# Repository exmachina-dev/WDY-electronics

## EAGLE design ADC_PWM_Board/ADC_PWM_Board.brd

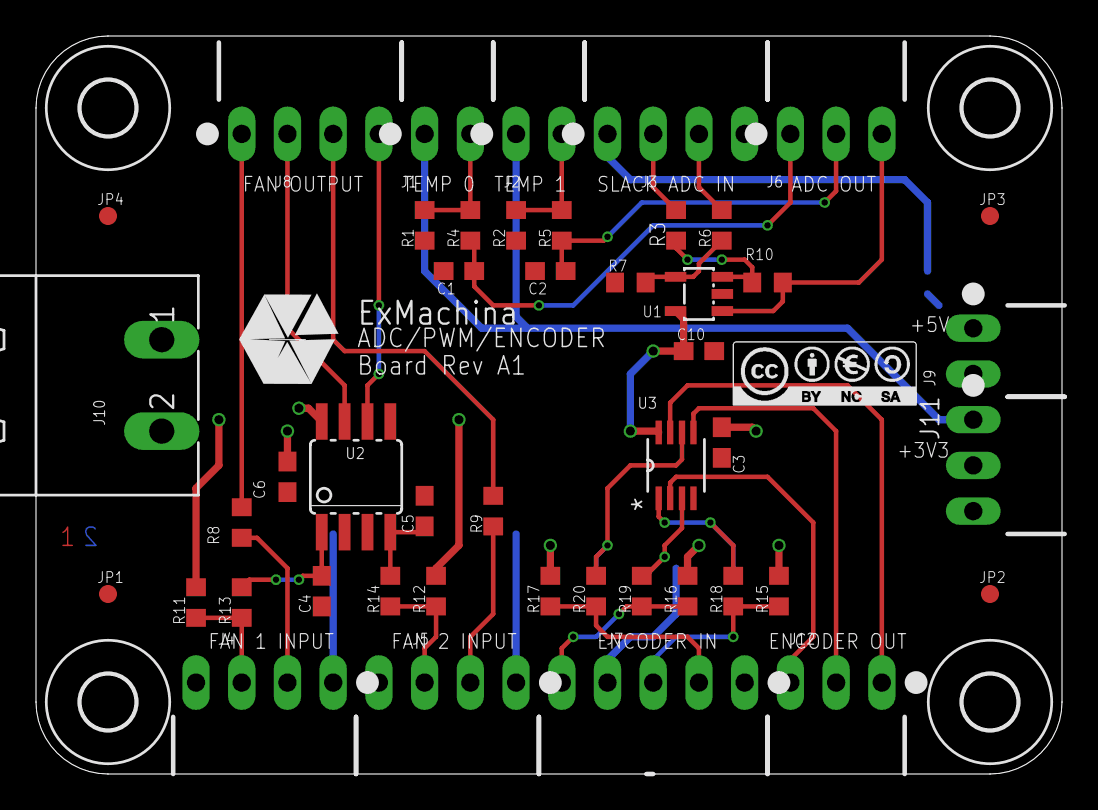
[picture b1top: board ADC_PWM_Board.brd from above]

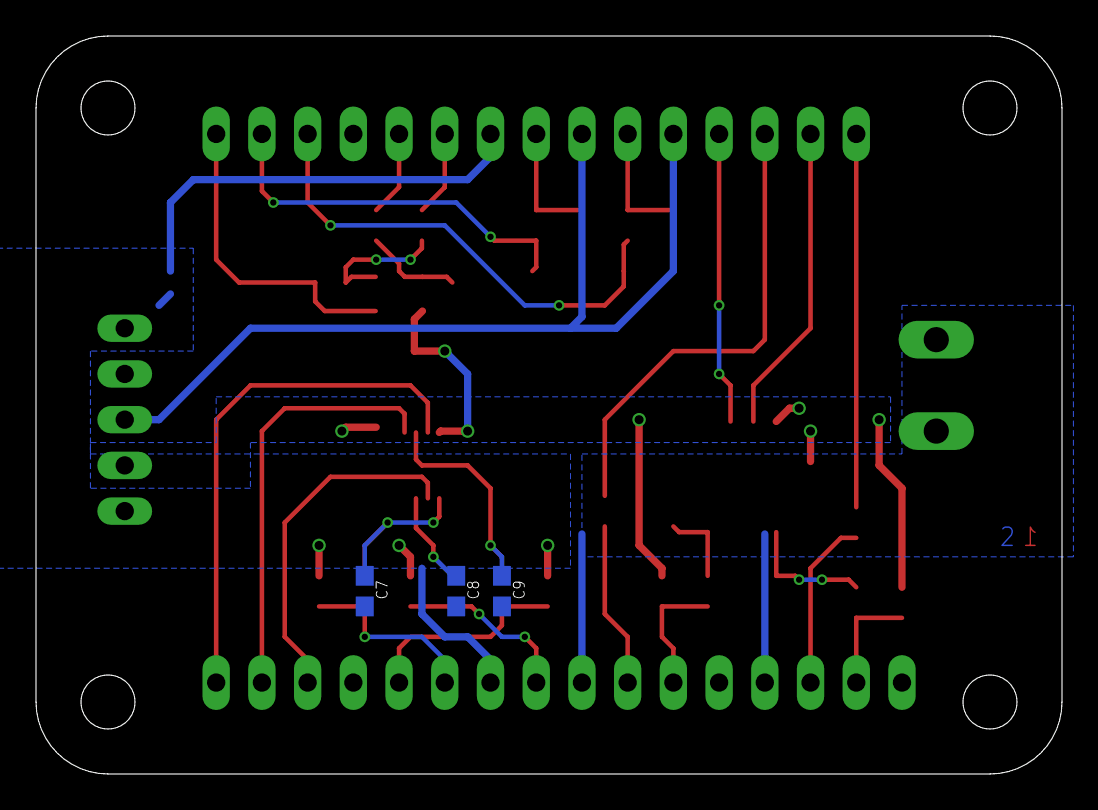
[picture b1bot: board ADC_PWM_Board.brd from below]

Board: 2 copper layers, 57.0 x 41.0 mm, 55 parts (3 on the bottom side), 33 nets.

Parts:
C1, C2, C3, C4, C5, C6, C7, C8, C9, C10: 0.1uF; C0603
CC1: CC-BY-NC-SA
H1, H2, H3, H4: MOUNT-HOLE3.0; 3,0
J1, J2, J9: 22-05-7028-02; 7395-02
J3, J4, J5, J8: 22-05-7048-04; 7395-04
J6, J11, J12: 22-05-7038-03; 7395-03
J7: 22-05-7058-05; 7395-05
J10: MSTBA2
JP1, JP2, JP3, JP4: FIDUCIAL1X2; FIDUCIAL-1X2
R1, R2: 10K; R0603
R3, R6: 1K8; R0603
R4, R5, R8, R9, R11, R12: 1K; R0603
R7, R10: 1K2; R0603
R13, R14, R18, R19, R20: 100; R0603
R15, R16, R17: 2K7; R0603
T1: EXMACHINA-LOGO-NAME; EXM-LOGO-BASELINE
U1: TLV313; SOT23-DBV
U2: HCPL0631; SOIC08
U3: SN74LVC3G17DCTR; SOP65P400X130-8N

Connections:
+3V3: C3.1, C6.1, C10.1, J11.2, R11.2, R12.2, U1.5, U2.8, U3.8
+5V: J3.1, J7.4, J9.1, R15.1, R16.1, R17.1
+24V: J4.1, J5.1, J10.1
ADC_SLACK_DETECTION: J6.3, R10.1, U1.1
ADC_TEMP_0: C1.1, J6.1, R4.1
ADC_TEMP_1: C2.1, J6.2, R5.2
AVDD: J1.1, J2.1, J11.1
ENCODER_A: J12.1, U3.7
ENCODER_B: J12.2, U3.5
ENCODER_Z: J12.3, U3.2
FAN_1_PWM: J8.1, R8.2
FAN_1_SENSOR: J8.2, U2.7
FAN_2_PWM: J8.3, R9.2
FAN_2_SENSOR: J8.4, U2.6
GND: C1.2, C2.2, C3.2, C4.2, C5.2, C6.2, C7.2, C8.2, C9.2, C10.2, J3.4, J4.4, J5.4, J7.1, J9.2, J10.2, J11.3, R1.1, R2.2, R7.1, U1.2, U2.2, U2.3, U2.5, U3.4
unnamed: J4.3, R11.1, R13.1
unnamed: J5.3, R12.1, R14.1
unnamed: C4.1, R13.2, U2.1
unnamed: C5.1, R14.2, U2.4
unnamed: J4.2, R8.1
unnamed: J5.2, R9.1
unnamed: J3.2, R3.1
unnamed: J7.3, R15.2, R18.1
unnamed: J7.5, R16.2, R19.1
unnamed: J7.2, R17.2, R20.1
unnamed: C9.1, R20.2, U3.6
unnamed: C8.1, R19.2, U3.3
unnamed: C7.1, R18.2, U3.1
unnamed: R3.2, R10.2, U1.3
unnamed: J1.2, R1.2, R4.2
unnamed: J2.2, R2.1, R5.1
unnamed: R6.2, R7.2, U1.4
unnamed: J3.3, R6.1

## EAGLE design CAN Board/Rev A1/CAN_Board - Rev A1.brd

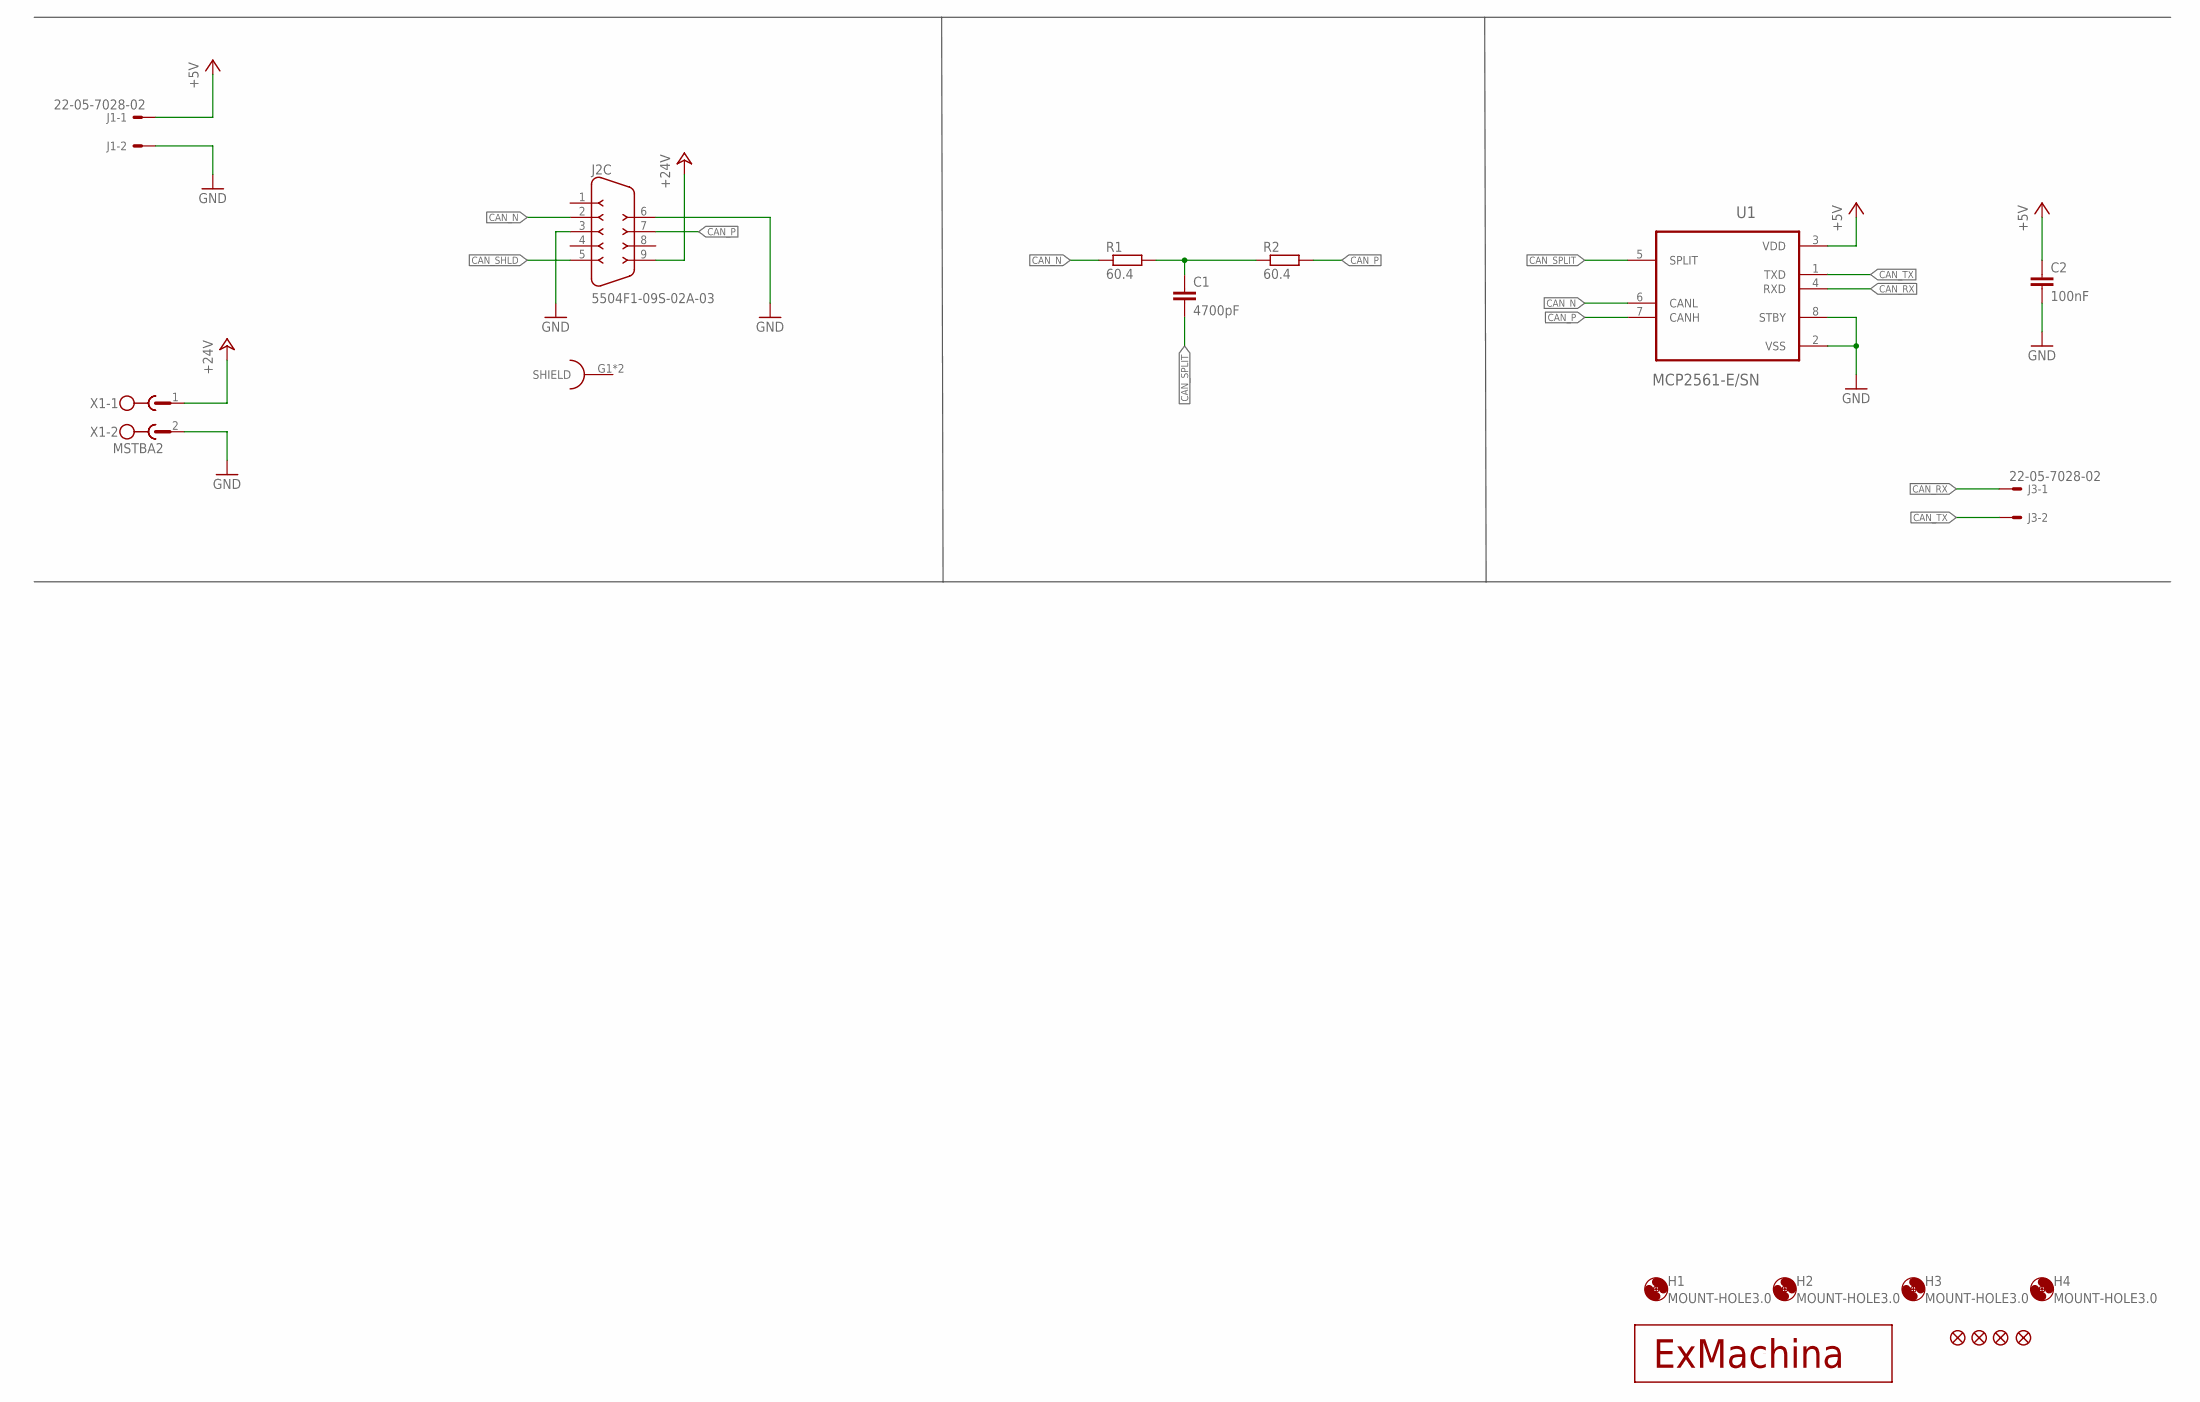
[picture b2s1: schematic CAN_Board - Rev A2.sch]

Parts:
C1: 4700pF; C0603; MPN MC0603B472K500CT
C2: 100nF; C0603; MPN MC0603B104K250CT
H1, H2, H3, H4: MOUNT-HOLE3.0; 3,0
J1, J3: 22-05-7028-02; 7395-02; MPN 22-05-7028
J2: 5504F1-09S-02A-03; 5504F1-09S-02A; MPN 5504F1-09S-02A-03
JP1, JP2, JP3, JP4: FIDUCIAL1X2; FIDUCIAL-1X2
R1, R2: 60.4; R0603; MPN MCMR06X60R4FTL
T1: EXMACHINA-LOGO-NAME; EXM-LOGO-BASELINE
U1: MCP2561-E/SN; SOIC127P600X175-8N; MPN MCP2561-E/SN
X1: MSTBA2

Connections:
+3V3: C2.1, J1.1, U1.3 (VDD)
+24V: J2.9, X1.1
CAN_N: J2.2, R1.1, U1.6 (CANL)
CAN_P: J2.7, R2.2, U1.7 (CANH)
CAN_RX: J3.1, U1.4 (RXD)
CAN_SHLD: J2.5
CAN_SPLIT: C1.2, U1.5 (SPLIT)
CAN_TX: J3.2, U1.1 (TXD)
GND: C2.2, J1.2, J2.3, J2.6, U1.2 (VSS), U1.8 (STBY), X1.2
unnamed: C1.1, R1.2, R2.1

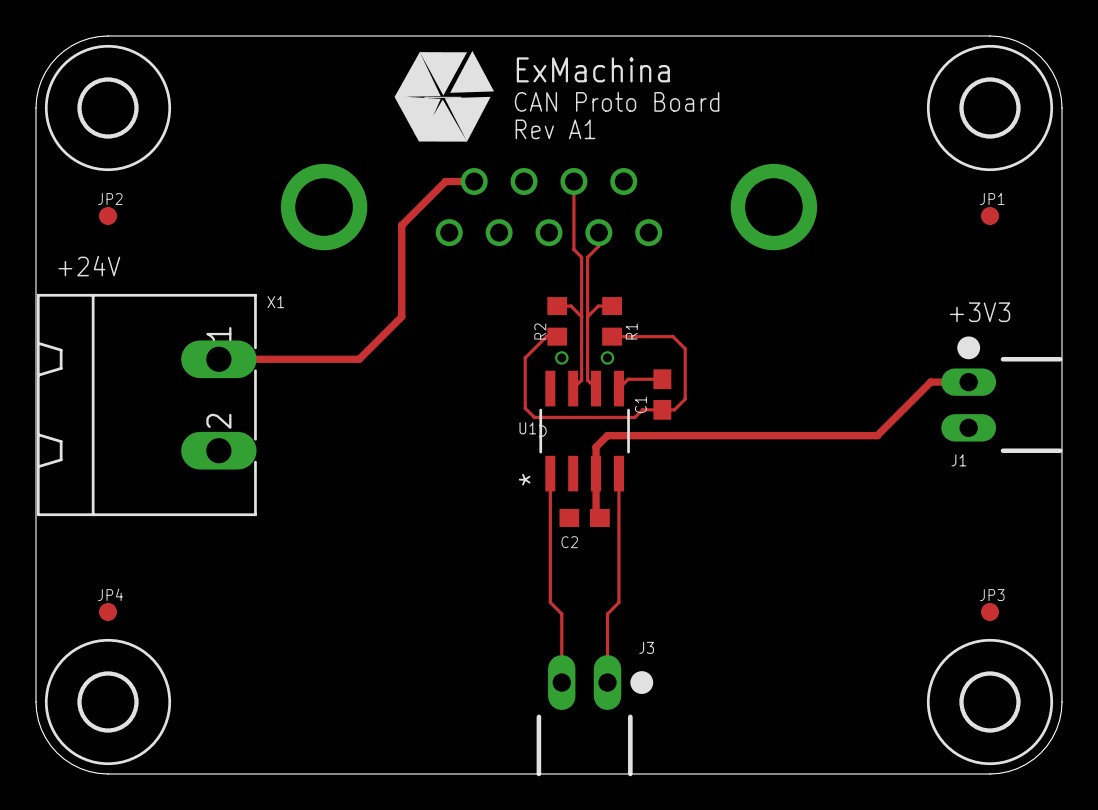
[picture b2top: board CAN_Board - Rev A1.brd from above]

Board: 2 copper layers, 57.0 x 41.0 mm, 18 parts (1 on the bottom side), 9 nets.

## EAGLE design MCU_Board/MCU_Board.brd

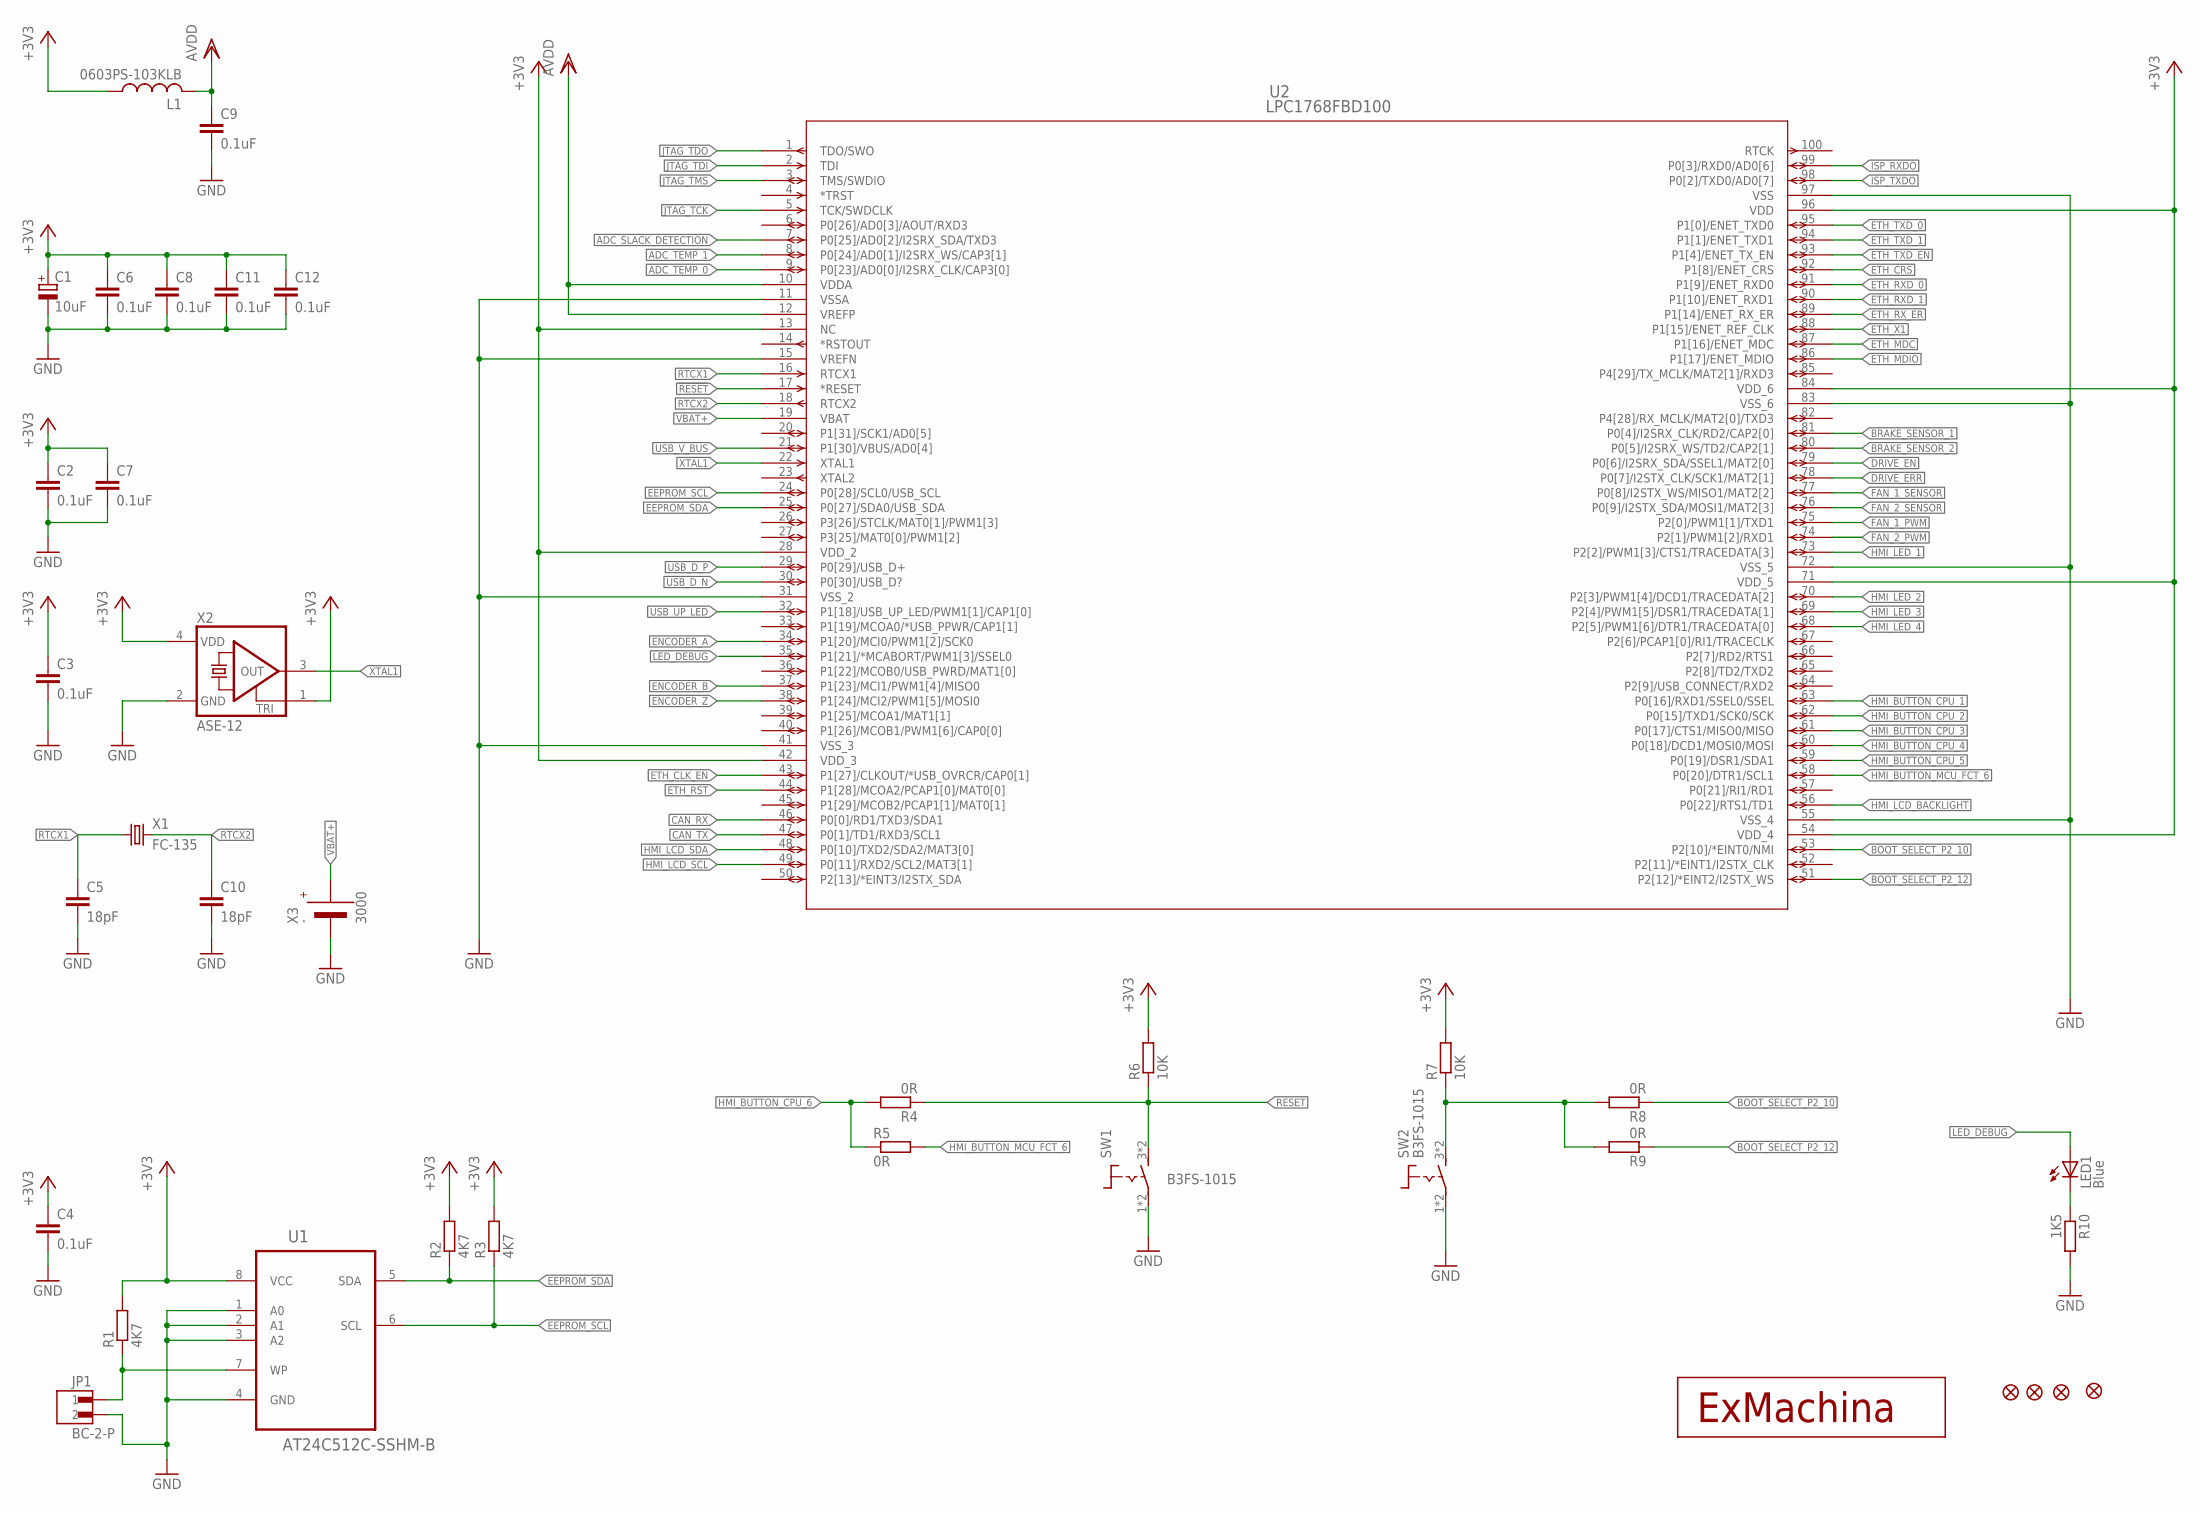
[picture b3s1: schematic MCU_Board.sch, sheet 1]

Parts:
C1: 10uF; CT3216
C2, C3, C4, C6, C7, C8, C9, C11, C12: 0.1uF; C0603
C5, C10: 18pF; C0603
JP1: BC-2-P
JP2, JP3, JP4, JP5: FIDUCIAL1X2; FIDUCIAL-1X2
L1: 0603PS-103KLB; 0603
LED1: Blue; CHIPLED_0603
R1, R2, R3: 4K7; R0603
R4, R5, R8, R9: 0R; R0603
R6, R7: 10K; R0603
R10: 1K5; R0603
SW1, SW2: B3FS-1015; B3FS
T2: EXMACHINA-LOGO-NAME; EXM-LOGO-BASELINE
U1: AT24C512C-SSHM-B; SOIC127P600X175-8N
U2: LPC1768FBD100; SOT407-1
X1: FC-135
X2: ASE-12; ASE
X3: 3000

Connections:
!RESET: U2.17 (*RESET)
ADC_SLACK_DETECTION: U2.7 (P0[25]/AD0[2]/I2SRX_SDA/TXD3); also elsewhere on the board
ADC_TEMP_0: U2.9 (P0[23]/AD0[0]/I2SRX_CLK/CAP3[0]); also elsewhere on the board
ADC_TEMP_1: U2.8 (P0[24]/AD0[1]/I2SRX_WS/CAP3[1]); also elsewhere on the board
BOOT_SELECT_P2_10: R8.1, U2.53 (P2[10]/*EINT0/NMI)
BOOT_SELECT_P2_12: R9.1, U2.51 (P2[12]/*EINT2/I2STX_WS)
BRAKE_SENSOR_1: U2.81 (P0[4]/I2SRX_CLK/RD2/CAP2[0]); also elsewhere on the board
BRAKE_SENSOR_2: U2.80 (P0[5]/I2SRX_WS/TD2/CAP2[1]); also elsewhere on the board
CAN_RX: U2.46 (P0[0]/RD1/TXD3/SDA1); also elsewhere on the board
CAN_TX: U2.47 (P0[1]/TD1/RXD3/SCL1); also elsewhere on the board
DRIVE_EN: U2.79 (P0[6]/I2SRX_SDA/SSEL1/MAT2[0]); also elsewhere on the board
DRIVE_ERR: U2.78 (P0[7]/I2STX_CLK/SCK1/MAT2[1]); also elsewhere on the board
EEPROM_SCL: R3.1, U1.6 (SCL), U2.24 (P0[28]/SCL0/USB_SCL)
EEPROM_SDA: R2.1, U1.5 (SDA), U2.25 (P0[27]/SDA0/USB_SDA)
ENCODER_A: U2.34 (P1[20]/MCI0/PWM1[2]/SCK0); also elsewhere on the board
ENCODER_B: U2.37 (P1[23]/MCI1/PWM1[4]/MISO0); also elsewhere on the board
ENCODER_Z: U2.38 (P1[24]/MCI2/PWM1[5]/MOSI0); also elsewhere on the board
ETH_CLK_EN: U2.43 (P1[27]/CLKOUT/*USB_OVRCR/CAP0[1])
ETH_CRS: U2.92 (P1[8]/ENET_CRS); also elsewhere on the board
ETH_MDC: U2.87 (P1[16]/ENET_MDC); also elsewhere on the board
ETH_MDIO: U2.86 (P1[17]/ENET_MDIO); also elsewhere on the board
ETH_RST: U2.44 (P1[28]/MCOA2/PCAP1[0]/MAT0[0]); also elsewhere on the board
ETH_RXD_0: U2.91 (P1[9]/ENET_RXD0); also elsewhere on the board
ETH_RXD_1: U2.90 (P1[10]/ENET_RXD1); also elsewhere on the board
ETH_RX_ER: U2.89 (P1[14]/ENET_RX_ER); also elsewhere on the board
ETH_TXD_0: U2.95 (P1[0]/ENET_TXD0); also elsewhere on the board
ETH_TXD_1: U2.94 (P1[1]/ENET_TXD1); also elsewhere on the board
ETH_TXD_EN: U2.93 (P1[4]/ENET_TX_EN); also elsewhere on the board
ETH_X1: U2.88 (P1[15]/ENET_REF_CLK); also elsewhere on the board
FAN_1_PWM: U2.75 (P2[0]/PWM1[1]/TXD1); also elsewhere on the board
FAN_1_SENSOR: U2.77 (P0[8]/I2STX_WS/MISO1/MAT2[2]); also elsewhere on the board
FAN_2_PWM: U2.74 (P2[1]/PWM1[2]/RXD1); also elsewhere on the board
FAN_2_SENSOR: U2.76 (P0[9]/I2STX_SDA/MOSI1/MAT2[3]); also elsewhere on the board
HMI_BUTTON_CPU_1: U2.63 (P0[16]/RXD1/SSEL0/SSEL); also elsewhere on the board
HMI_BUTTON_CPU_2: U2.62 (P0[15]/TXD1/SCK0/SCK); also elsewhere on the board
HMI_BUTTON_CPU_3: U2.61 (P0[17]/CTS1/MISO0/MISO); also elsewhere on the board
HMI_BUTTON_CPU_4: U2.60 (P0[18]/DCD1/MOSI0/MOSI); also elsewhere on the board
HMI_BUTTON_CPU_5: U2.59 (P0[19]/DSR1/SDA1); also elsewhere on the board
HMI_BUTTON_CPU_6: R4.2, R5.1; also elsewhere on the board
HMI_BUTTON_MCU_FCT_6: R5.2, U2.58 (P0[20]/DTR1/SCL1)
HMI_LCD_BACKLIGHT: U2.56 (P0[22]/RTS1/TD1); also elsewhere on the board
HMI_LCD_SCL: U2.49 (P0[11]/RXD2/SCL2/MAT3[1]); also elsewhere on the board
HMI_LCD_SDA: U2.48 (P0[10]/TXD2/SDA2/MAT3[0]); also elsewhere on the board
HMI_LED_1: U2.73 (P2[2]/PWM1[3]/CTS1/TRACEDATA[3]); also elsewhere on the board
HMI_LED_2: U2.70 (P2[3]/PWM1[4]/DCD1/TRACEDATA[2]); also elsewhere on the board
HMI_LED_3: U2.69 (P2[4]/PWM1[5]/DSR1/TRACEDATA[1]); also elsewhere on the board
HMI_LED_4: U2.68 (P2[5]/PWM1[6]/DTR1/TRACEDATA[0]); also elsewhere on the board
ISP_RXDO: U2.99 (P0[3]/RXD0/AD0[6]); also elsewhere on the board
ISP_TXDO: U2.98 (P0[2]/TXD0/AD0[7]); also elsewhere on the board
JTAG_TCK: U2.5 (TCK/SWDCLK); also elsewhere on the board
JTAG_TDI: U2.2 (TDI); also elsewhere on the board
JTAG_TDO: U2.1 (TDO/SWO); also elsewhere on the board
JTAG_TMS: U2.3 (TMS/SWDIO); also elsewhere on the board
LED_DEBUG: LED1.A, U2.35 (P1[21]/*MCABORT/PWM1[3]/SSEL0)
unnamed: R7.1, R8.2, R9.2, SW2.3 (1), SW2.4 (1)
unnamed: JP1.1, R1.1, U1.7 (WP)
unnamed: LED1.C, R10.1
RESET: R4.1, R6.1, SW1.3 (1), SW1.4 (1); also elsewhere on the board
RTCX1: C5.1, U2.16 (RTCX1), X1.1
RTCX2: C10.1, U2.18 (RTCX2), X1.2
USB_D_N: U2.30 (P0[30]/USB_D?); also elsewhere on the board
USB_D_P: U2.29 (P0[29]/USB_D+); also elsewhere on the board
USB_UP_LED: U2.32 (P1[18]/USB_UP_LED/PWM1[1]/CAP1[0]); also elsewhere on the board
USB_V_BUS: U2.21 (P1[30]/VBUS/AD0[4]); also elsewhere on the board
VBAT+: U2.19 (VBAT), X3.+1 (VBAT+), X3.+2 (VBAT+)
XTAL1: U2.22 (XTAL1), X2.3 (OUT)

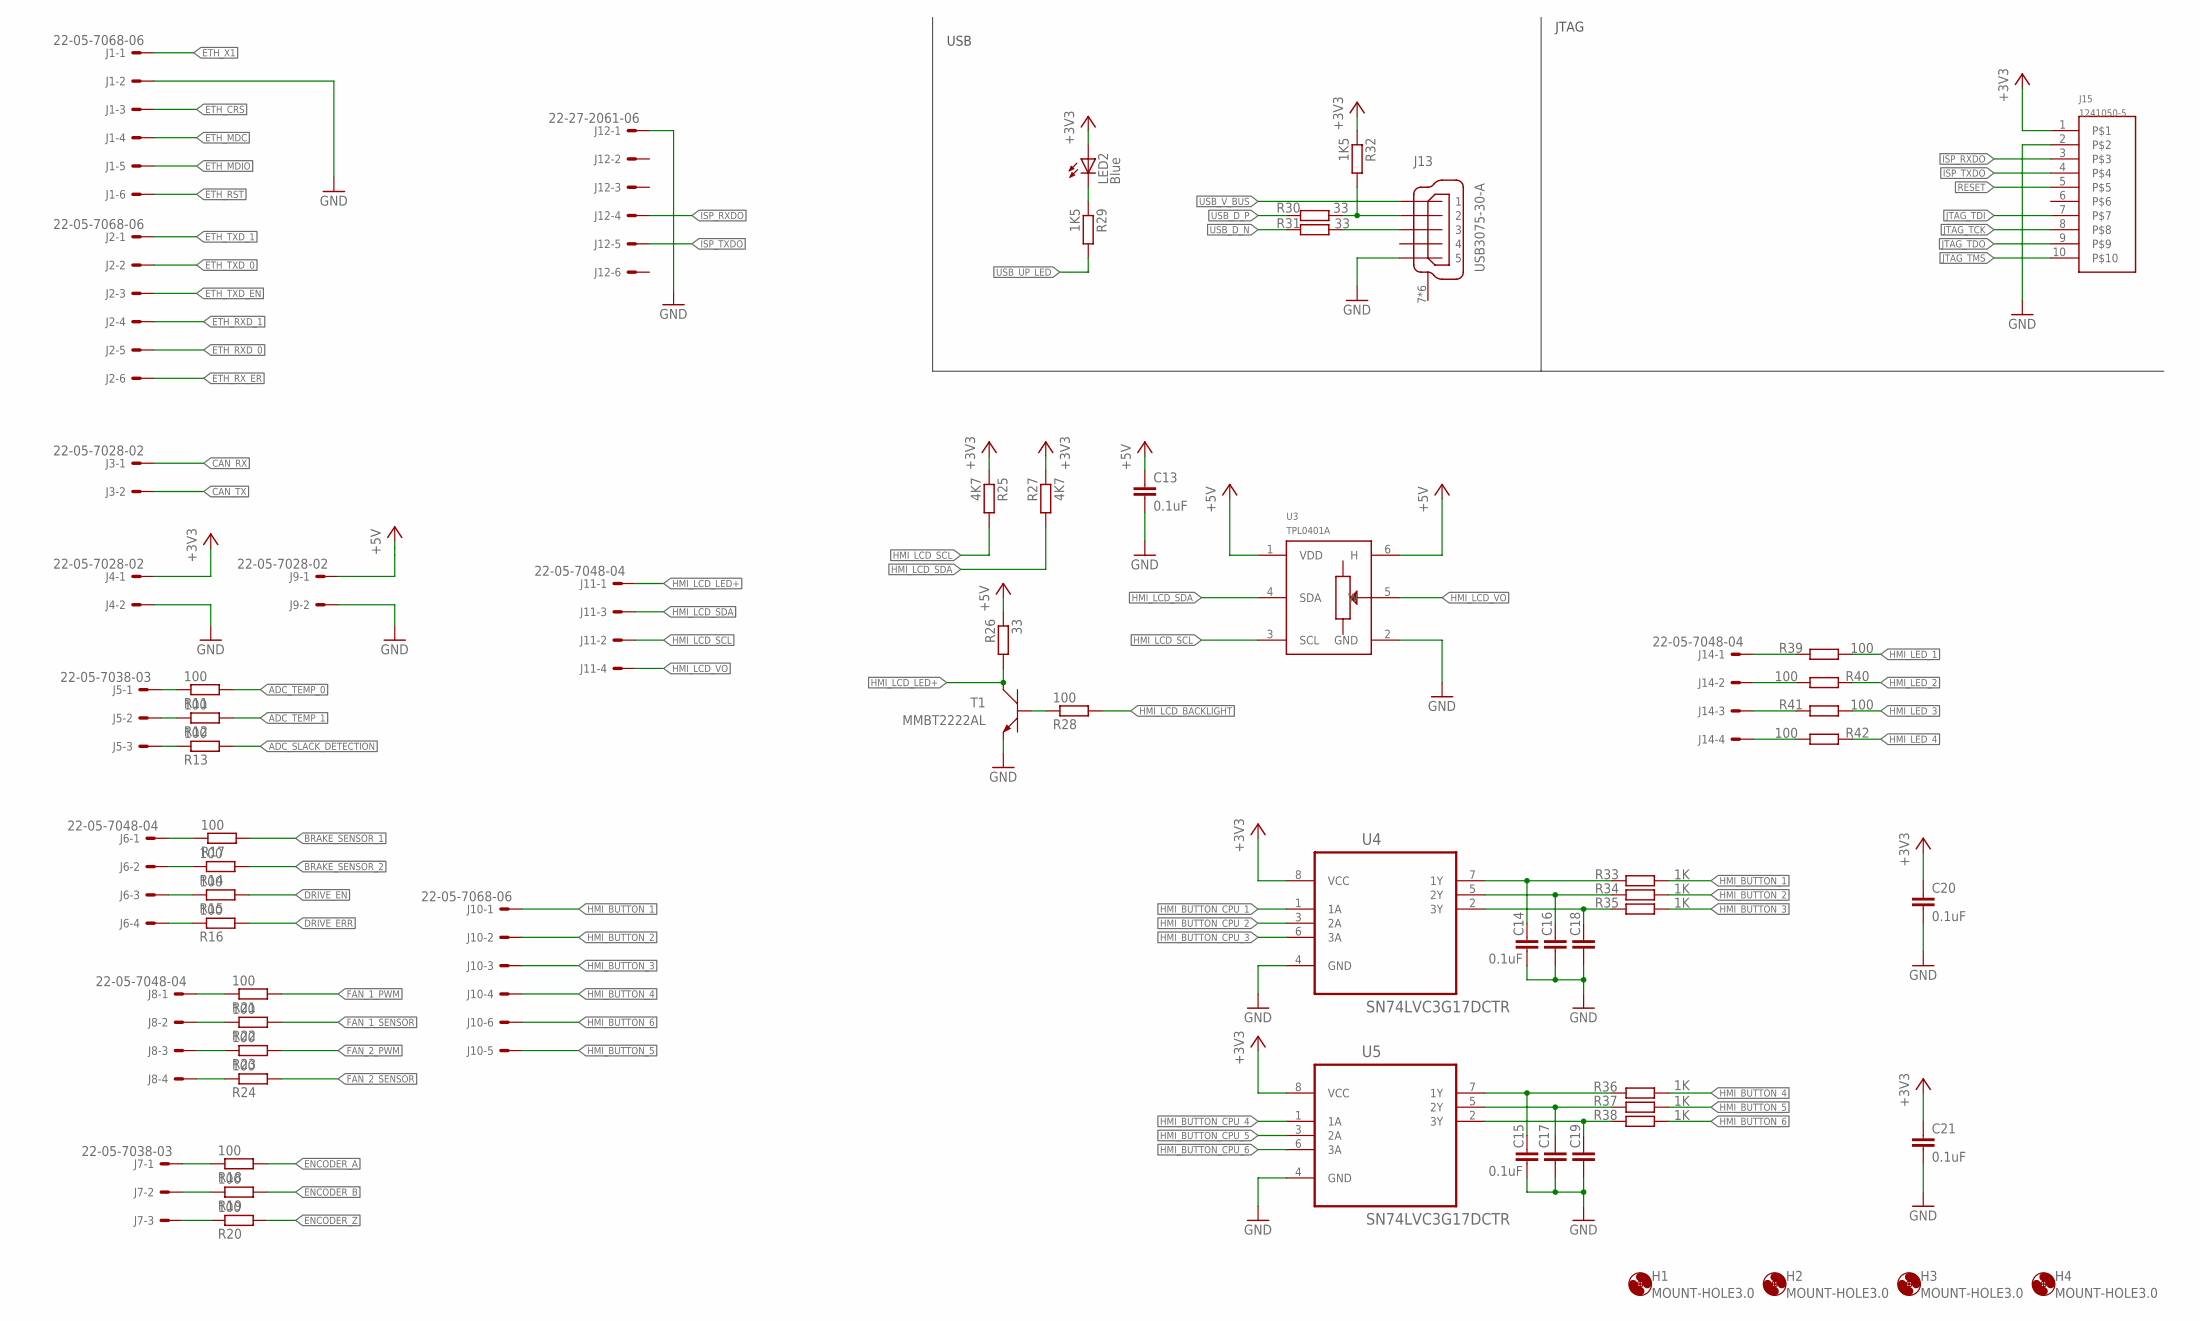
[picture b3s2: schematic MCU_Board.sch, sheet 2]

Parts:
C13, C14, C15, C16, C17, C18, C19, C20, C21: 0.1uF; C0603
H1, H2, H3, H4: MOUNT-HOLE3.0; 3,0
J1, J2, J10: 22-05-7068-06; 7395-06
J3, J4, J9: 22-05-7028-02; 7395-02
J5, J7: 22-05-7038-03; 7395-03
J6, J8, J11, J14: 22-05-7048-04; 7395-04
J12: 22-27-2061-06; 6410-06
J13: USB3075-30-A; USB_MICROB_SMT
J15: 1241050-5; 2.54/2X5
LED2: Blue; CHIPLED_0603
R11, R12, R13, R14, R15, R16, R17, R18, R19, R20, R21, R22, R23, R24, R28, R39, R40, R41, R42: 100; R0603
R25, R27: 4K7; R0603
R26, R30, R31: 33; R0603
R29, R32: 1K5; R0603
R33, R34, R35, R36, R37, R38: 1K; R0603
T1: MMBT2222AL; SOT−23
U3: TPL0401A; SC-70-DCK
U4, U5: SN74LVC3G17DCTR; SOP65P400X130-8N

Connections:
+5V: C13.1, J9.1, R26.1, U3.1 (VDD), U3.6 (H)
ADC_SLACK_DETECTION: R13.2; also elsewhere on the board
ADC_TEMP_0: R11.2; also elsewhere on the board
ADC_TEMP_1: R12.2; also elsewhere on the board
BRAKE_SENSOR_1: R17.2; also elsewhere on the board
BRAKE_SENSOR_2: R14.2; also elsewhere on the board
CAN_RX: J3.1; also elsewhere on the board
CAN_TX: J3.2; also elsewhere on the board
DRIVE_EN: R15.2; also elsewhere on the board
DRIVE_ERR: R16.2; also elsewhere on the board
ENCODER_A: R18.2; also elsewhere on the board
ENCODER_B: R19.2; also elsewhere on the board
ENCODER_Z: R20.2; also elsewhere on the board
ETH_CRS: J1.3; also elsewhere on the board
ETH_MDC: J1.4; also elsewhere on the board
ETH_MDIO: J1.5; also elsewhere on the board
ETH_RST: J1.6; also elsewhere on the board
ETH_RXD_0: J2.5; also elsewhere on the board
ETH_RXD_1: J2.4; also elsewhere on the board
ETH_RX_ER: J2.6; also elsewhere on the board
ETH_TXD_0: J2.2; also elsewhere on the board
ETH_TXD_1: J2.1; also elsewhere on the board
ETH_TXD_EN: J2.3; also elsewhere on the board
ETH_X1: J1.1; also elsewhere on the board
FAN_1_PWM: R21.2; also elsewhere on the board
FAN_1_SENSOR: R22.2; also elsewhere on the board
FAN_2_PWM: R23.2; also elsewhere on the board
FAN_2_SENSOR: R24.2; also elsewhere on the board
HMI_BUTTON_1: J10.1, R33.1
HMI_BUTTON_2: J10.2, R34.1
HMI_BUTTON_3: J10.3, R35.1
HMI_BUTTON_4: J10.4, R36.1
HMI_BUTTON_5: J10.5, R37.1
HMI_BUTTON_6: J10.6, R38.1
HMI_BUTTON_CPU_1: U4.1 (1A); also elsewhere on the board
HMI_BUTTON_CPU_2: U4.3 (2A); also elsewhere on the board
HMI_BUTTON_CPU_3: U4.6 (3A); also elsewhere on the board
HMI_BUTTON_CPU_4: U5.1 (1A); also elsewhere on the board
HMI_BUTTON_CPU_5: U5.3 (2A); also elsewhere on the board
HMI_BUTTON_CPU_6: U5.6 (3A); also elsewhere on the board
HMI_LCD_BACKLIGHT: R28.2; also elsewhere on the board
HMI_LCD_LED+: J11.1, R26.2, T1.3 (C)
HMI_LCD_SCL: J11.2, R25.2, U3.3 (SCL); also elsewhere on the board
HMI_LCD_SDA: J11.3, R27.2, U3.4 (SDA); also elsewhere on the board
HMI_LCD_VO: J11.4, U3.5 (W)
HMI_LED_1: R39.1; also elsewhere on the board
HMI_LED_2: R40.2; also elsewhere on the board
HMI_LED_3: R41.1; also elsewhere on the board
HMI_LED_4: R42.2; also elsewhere on the board
ISP_RXDO: J12.4, J15.3; also elsewhere on the board
ISP_TXDO: J12.5, J15.4; also elsewhere on the board
JTAG_TCK: J15.8; also elsewhere on the board
JTAG_TDI: J15.7; also elsewhere on the board
JTAG_TDO: J15.9; also elsewhere on the board
JTAG_TMS: J15.10; also elsewhere on the board
unnamed: J14.2, R40.1
unnamed: J14.4, R42.1
unnamed: J7.1, R18.1
unnamed: J7.2, R19.1
unnamed: J7.3, R20.1
unnamed: R28.1, T1.1 (B)
unnamed: J8.1, R21.1
unnamed: J8.2, R22.1
unnamed: J8.3, R23.1
unnamed: J8.4, R24.1
unnamed: J5.3, R13.1
unnamed: J5.2, R12.1
unnamed: J5.1, R11.1
unnamed: J13.2, R30.1, R32.2
unnamed: J13.3, R31.1
unnamed: C14.1, R33.2, U4.7 (1Y)
unnamed: LED2.C, R29.1
unnamed: C16.1, R34.2, U4.5 (2Y)
unnamed: C18.1, R35.2, U4.2 (3Y)
unnamed: J6.4, R16.1
unnamed: J6.3, R15.1
unnamed: J6.2, R14.1
unnamed: C15.1, R36.2, U5.7 (1Y)
unnamed: C17.1, R37.2, U5.5 (2Y)
unnamed: C19.1, R38.2, U5.2 (3Y)
unnamed: J6.1, R17.1
unnamed: J14.1, R39.2
unnamed: J14.3, R41.2
RESET: J15.5; also elsewhere on the board
USB_D_N: R31.2; also elsewhere on the board
USB_D_P: R30.2; also elsewhere on the board
USB_UP_LED: R29.2; also elsewhere on the board
USB_V_BUS: J13.1; also elsewhere on the board

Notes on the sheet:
USB
JTAG

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
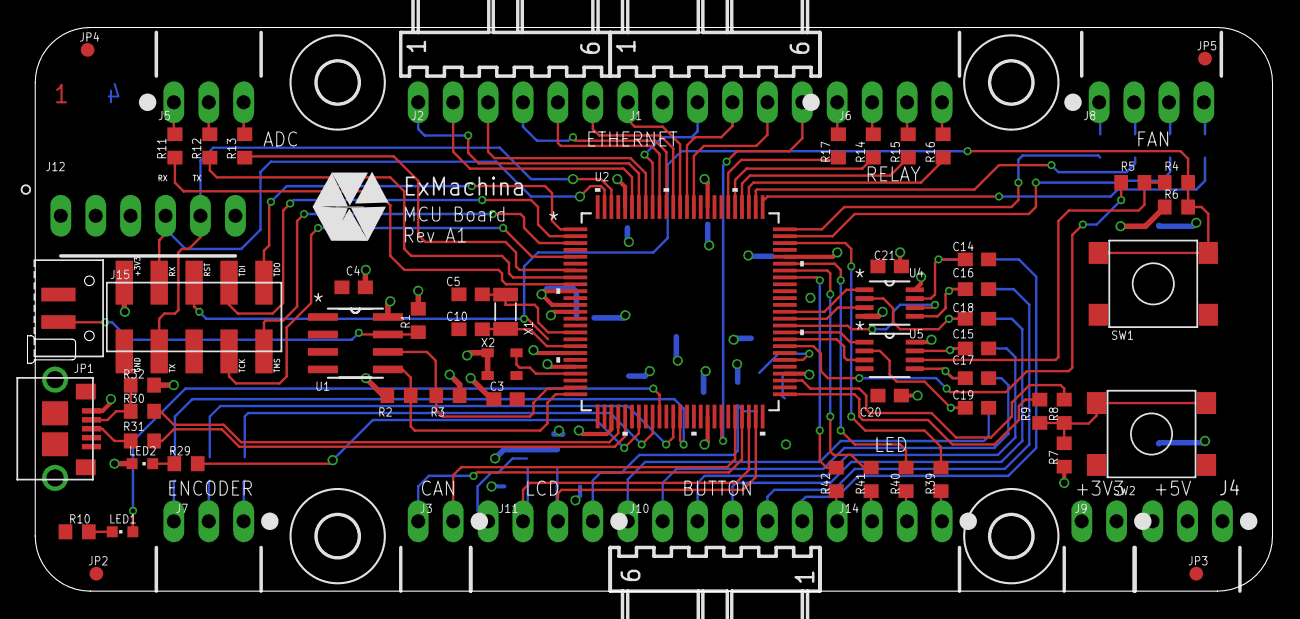
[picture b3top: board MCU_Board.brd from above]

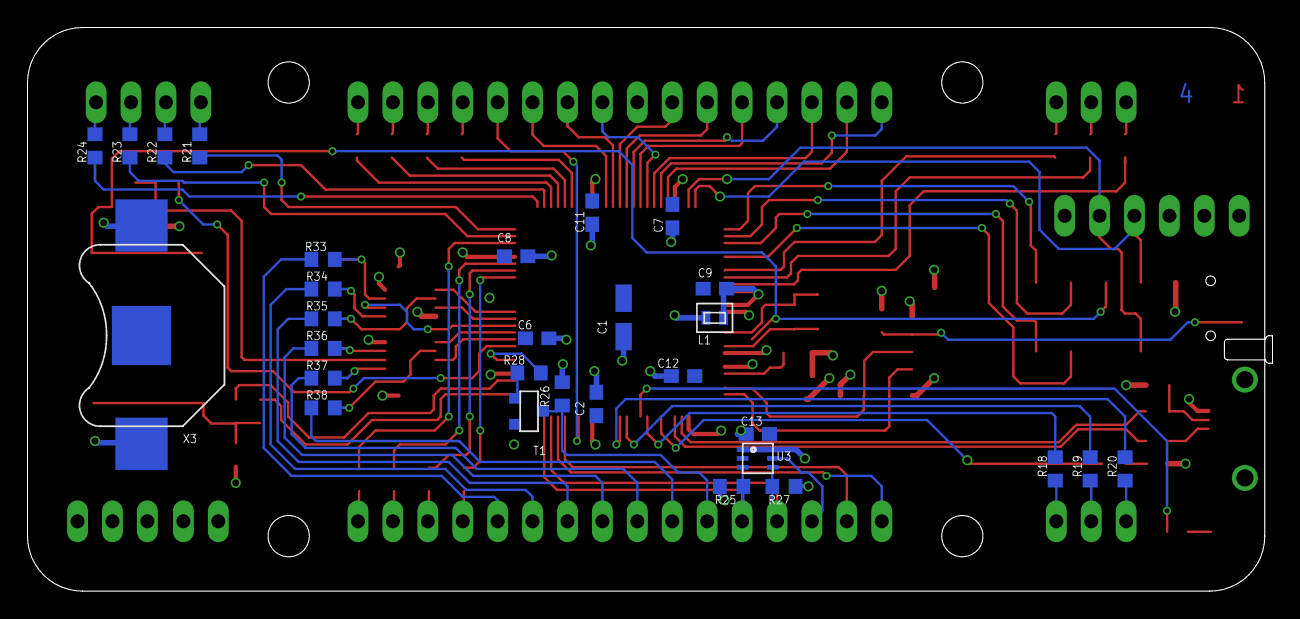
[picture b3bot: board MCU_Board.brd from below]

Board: 4 copper layers, 90.6 x 41.0 mm, 102 parts (30 on the bottom side), 104 nets.

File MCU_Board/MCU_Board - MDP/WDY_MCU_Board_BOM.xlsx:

Qty | Value | Device | Package | Parts | Description | MPN
1 | 0603PS-103KLB | 0603PS | 603 | L1 | INDUCTANCE | 0603PS-103KLB
1 | 3000 | 3000 | 3000 | X3 |  | 3000
1 | 22-27-2061-06 | 22-27-2061-06 | 1647397 | J12 | CONNECTOR | 22-27-2061
2 | 22-05-7028-02 | 22-05-7028-02 | 2007041 | J3, J9 | CONNECTOR | 22-05-7028
3 | 22-05-7038-03 | 22-05-7038-03 | 2007069 | J4, J5, J7 | CONNECTOR | 22-05-7038
4 | 22-05-7048-04 | 22-05-7048-04 | 2007100 | J6, J8, J11, J14 | CONNECTOR | 22-05-7048
3 | 22-05-7068-06 | 22-05-7068-06 | 2007161 | J1, J2, J10 | CONNECTOR | 22-05-7068
1 | 1241050-5 | 1241050-5 | 2.54/2X5 | J15 | CONNECTOR | 1241050-5
1 | ASE-12 | ASE | ASE | X2 | 3.3Vdc CMOS SMD CRYSTAL CLOCK OSCILLATOR | ASE-12.000MHZ-LC-T
2 | B3FS-1015 | B3FS-1015 | B3FS | SW1, SW2 | Surface-mounting Switches Ideal for | B3FS1015
18 | 0.1uF | C-EUC0603 | C0603 | C2, C3, C4, C6, C7, C8, C9, C11, C12, C13, C14, C15, C16, C17, C18, C19, C20, C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 | CAPACITOR, European symbol | MC0603B104K160CT
2 | 18pF | C-EUC0603 | C0603 | C5, C10 | CAPACITOR, European symbol | MC0603N180K500CT
2 | Blue | LEDCHIPLED_0603 | CHIPLED_0603 | LED1, LED2 | LED | OVS-0603
1 | 10uF | CPOL-EUCT3216 | CT3216 | C1 | POLARIZED CAPACITOR, European symbol | F931A106MAA
1 | FC-135 | FC-135 | FC-135 | X1 | 32.768kHz ｱ20ppm Crystal 12.5pF 70 kOhm -40ｰC ~ 85ｰC Surface Mount 2-SMD | Q13FC13500004
3 | 33 | R-EU_R0603 | R0603 | R26, R30, R31 | RESISTOR, European symbol | MCMR06X33R0FTL
19 | 100 | R-EU_R0603 | R0603 | R11, R12, R13, R14, R15, R16, R17, R18, R19, R20, R21, R22, R23, R24, R28, R39,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 | RESISTOR, European symbol | MCMR06X1000FTL
4 | 0R | R-EU_R0603 | R0603 | R4, R5, R8, R9 | RESISTOR, European symbol | MCMR06X000 PTL
2 | 10K | R-EU_R0603 | R0603 | R6, R7 | RESISTOR, European symbol | MCMR06X1002FTL
6 | 1K | R-EU_R0603 | R0603 | R33, R34, R35, R36, R37, R38 | RESISTOR, European symbol | MCMR06X1001FTL
3 | 1K5 | R-EU_R0603 | R0603 | R10, R29, R32 | RESISTOR, European symbol | MCMR06X1501FTL
5 | 4K7 | R-EU_R0603 | R0603 | R1, R2, R3, R25, R27 | RESISTOR, European symbol | MCMR06X4701FTL
1 | TPL0401A | TPL0401A | SC-70-DCK | U3 | DIGITAL POTENTIOMETER | ISL90728WIE627Z-TK
1 | AT24C512C-SSHM-B | AT24C512C-SSHM-B | SOIC127P600X175-8N | U1 | SERIAL EEPROM IC Memory Size:512Kbit,8-SOIC | AT24C02C-SSHM-B
2 | SN74LVC3G17DCTR | SN74LVC3G17DCTR | SOP65P400X130-8N | U4, U5 | TRIPLE SCHMITT-TRIGGER BUFFER | SN74LVC3G17DCTR
1 | MMBT2222AL | MMBT2222AL | SOT-23 | T1 | General Purpose Transistors | MMBT2222ALT1G
1 | LPC1768FBD100 | LPC1768FBD100 | SOT407-1 | U2 | MCU Cortex M3 | LPC1768FBD100
1 | USB3075-30-A | USB3075-30-A | USB_MICROB_SMT | J13 | CONNECTOR | USB3075-30-A

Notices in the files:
parts and their libraries:
COPYRIGHT: Copyright C 2015 Accelerated Designs. All rights reserved
Wurth-POWER_MAGNETICS-rev16f: Copyright: Würth Elektronik
